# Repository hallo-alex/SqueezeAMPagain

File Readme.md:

# SqueezeAMPagain

As github annoys me with their 2FA policy I'm moving this to [codeberg](https://codeberg.org/hallo-alex/SqueezeAMPagain)

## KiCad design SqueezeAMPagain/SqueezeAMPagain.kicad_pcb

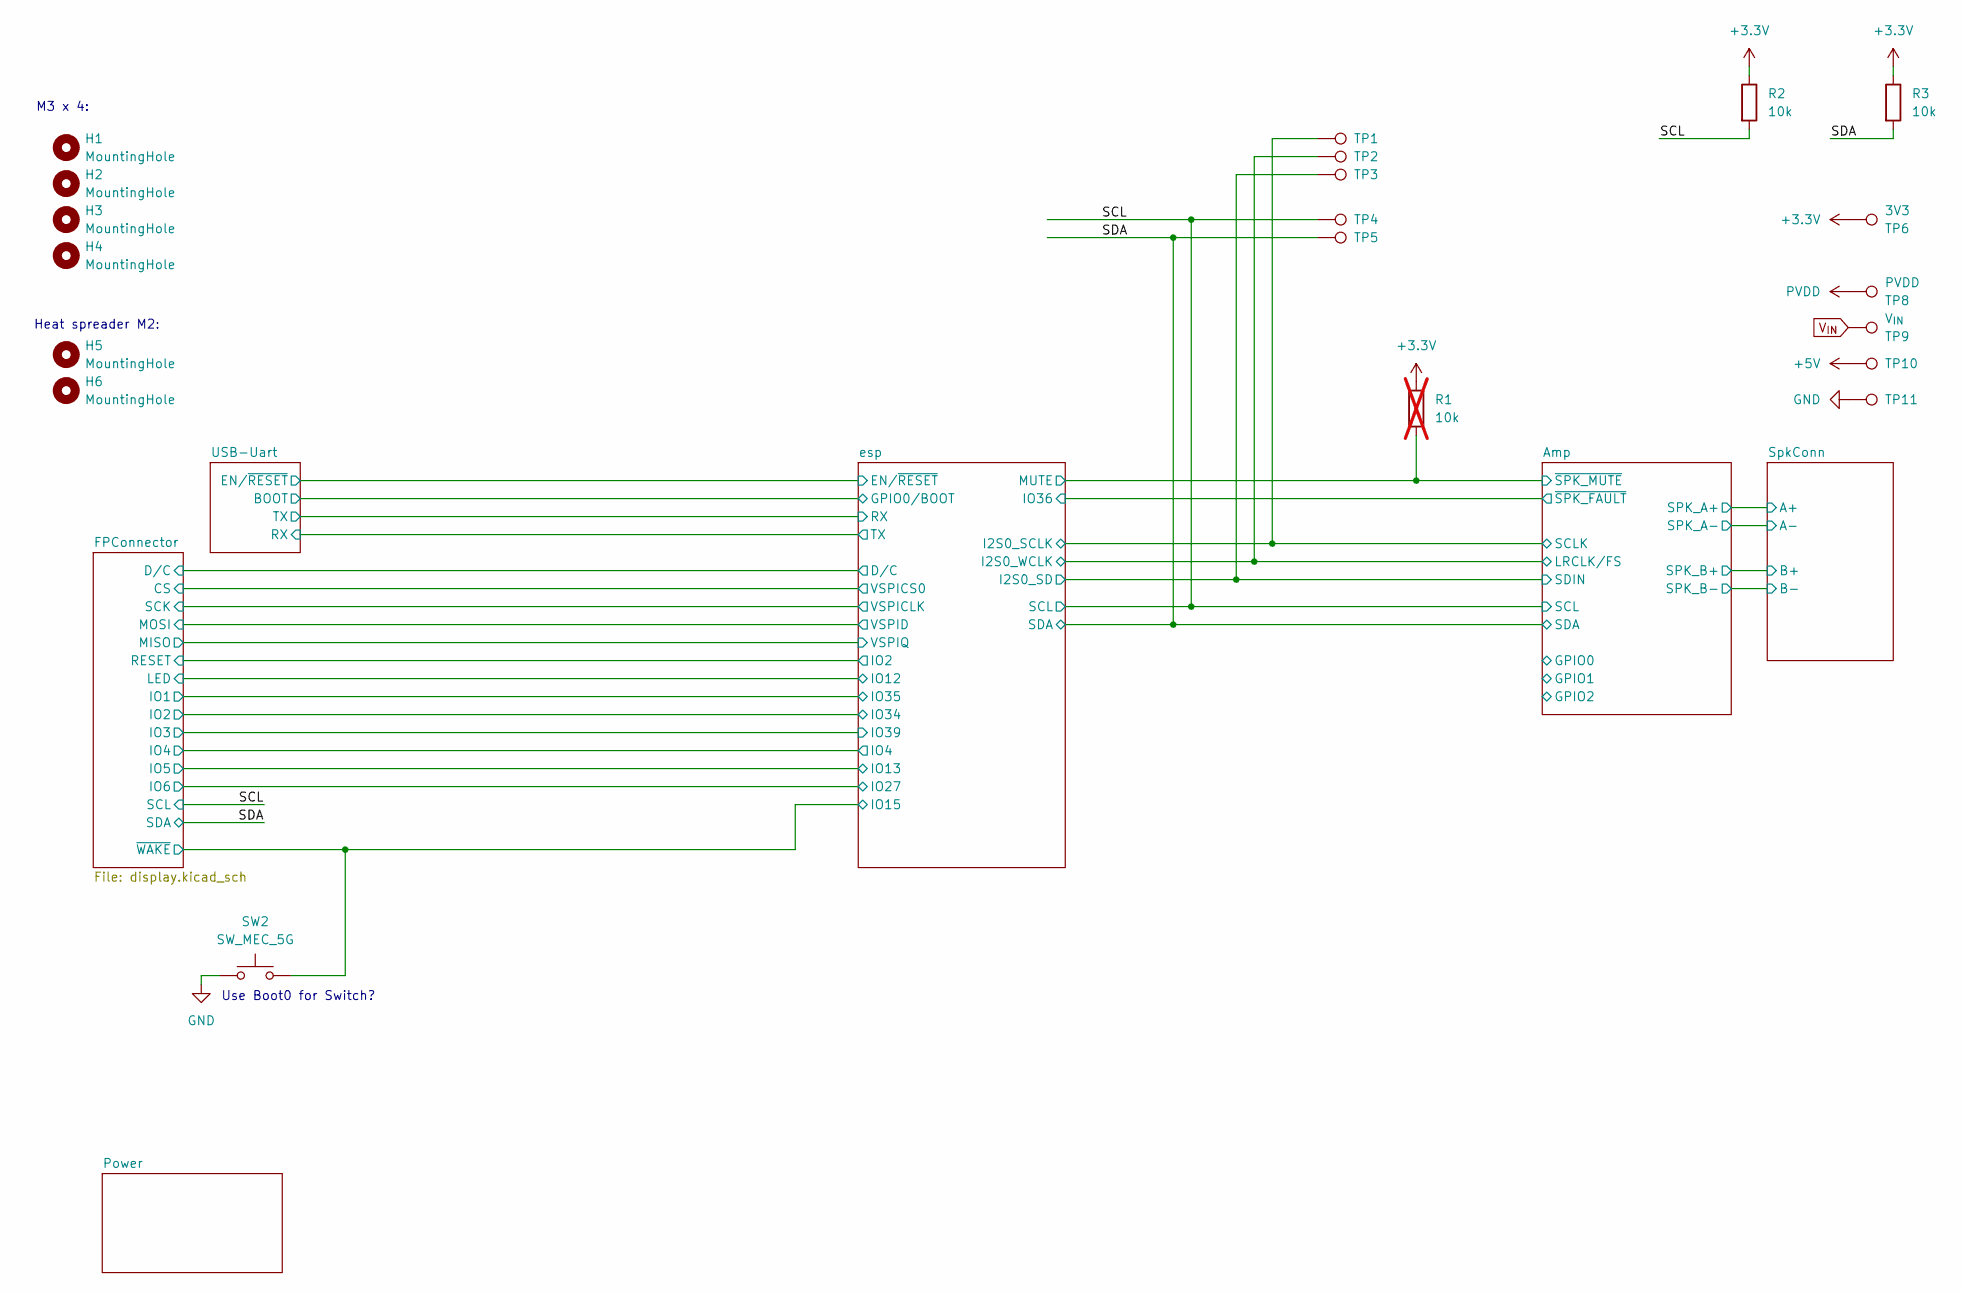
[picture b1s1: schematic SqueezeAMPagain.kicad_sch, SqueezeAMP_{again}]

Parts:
H1, H2, H3, H4: MountingHole; MountingHole_3.2mm_M3
H5, H6: MountingHole; MountingHole_2.5mm
R1: 10k; R_0402_1005Metric; JLCPCB# C25804; not fitted
R2, R3: 10k; R_0402_1005Metric; JLCPCB# C25804
SW2: SW_MEC_5G; SW_Push_1P1T_XKB_TS-1187A
TP1, TP2, TP3, TP4, TP5, TP10: TestPoint_Pad_D1.0mm
TP6: 3V3; TestPoint_Pad_D1.0mm
TP8: PVDD; TestPoint_Pad_D1.0mm
TP9: V_{IN}; TestPoint_Pad_D1.0mm
TP11: TestPoint_THTPad_D1.0mm_Drill0.5mm

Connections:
+3.3V: R1.1, R2.1, R3.1, TP6.1; also elsewhere on the board
+5V: TP10.1; also elsewhere on the board
/Amp/LRCLK/FS: TP2.1; also elsewhere on the board
/Amp/SCLK: TP1.1; also elsewhere on the board
/Amp/SDIN: TP3.1; also elsewhere on the board
/FPConnector/~WAKE: SW2.3 (B), SW2.4 (B); also elsewhere on the board
/SCL: R2.2, TP4.1; also elsewhere on the board
/SDA: R3.2, TP5.1; also elsewhere on the board
/esp/TMS: R1.2; also elsewhere on the board
GND: SW2.1 (A), SW2.2 (A), TP11.1; also elsewhere on the board
PVDD: TP8.1; also elsewhere on the board
V_{IN}: TP9.1

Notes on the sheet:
M3 x 4:
Use Boot0 for Switch?
Heat spreader M2:

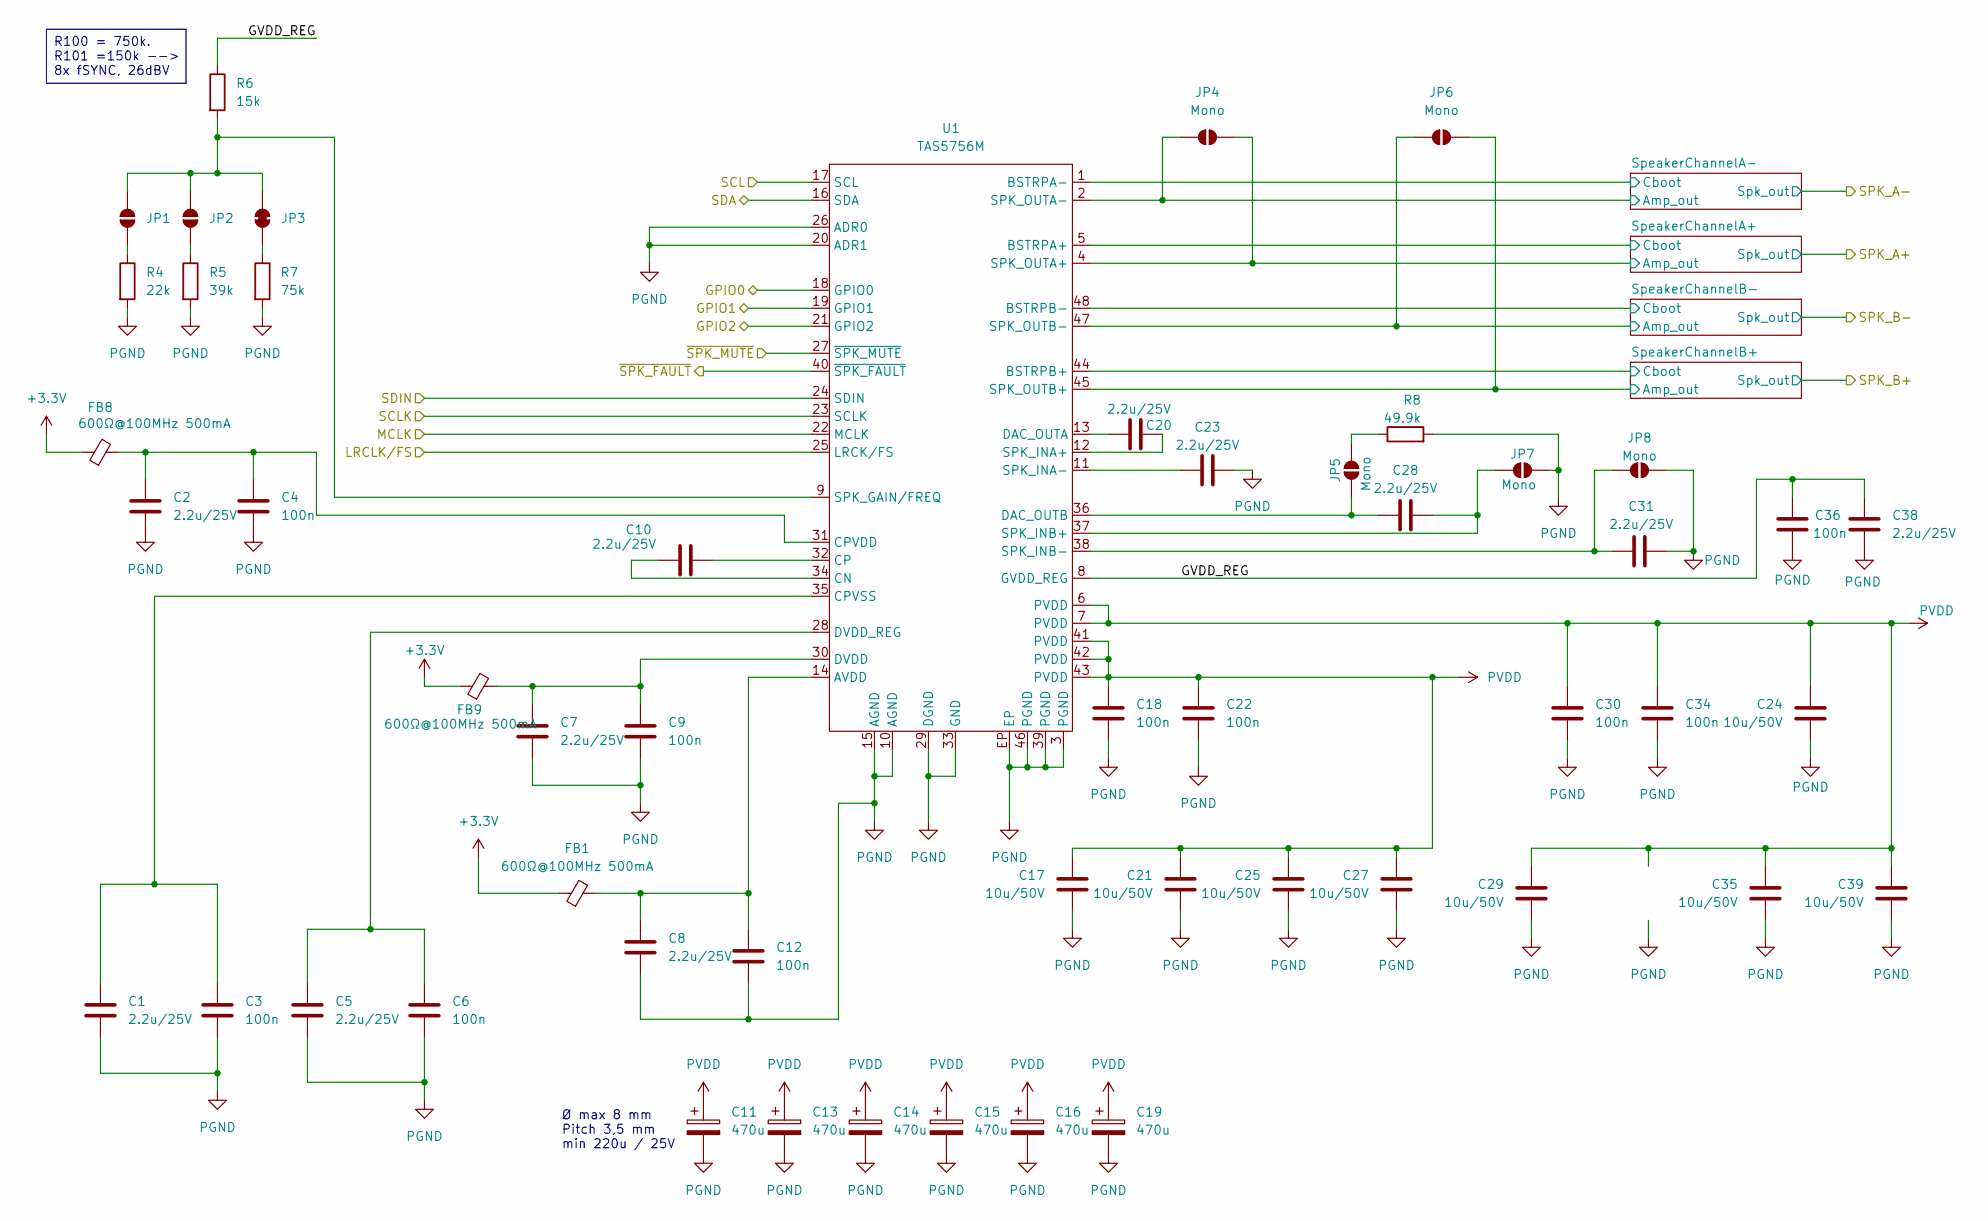
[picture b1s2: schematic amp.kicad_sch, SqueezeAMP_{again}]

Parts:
C1, C2, C5, C7, C8, C10, C20, C23, C28, C31, C38: 2.2u/25V; C_0805_2012Metric
C3, C4, C6, C9, C12: 100n; C_0402_1005Metric
C11, C13, C14, C15, C16, C19: 470u; CP_Radial_D8.0mm_P3.50mm
C17, C21, C24, C25, C27, C29, C35, C39: 10u/50V; C_1206_3216Metric
C18, C22, C30, C34, C36: 100n; C_0603_1608Metric
FB1, FB8, FB9: 600Ω@100MHz 500mA; L_0805_2012Metric; JLCPCB# C1017
JP1, JP2: SolderJumper_2_Open; SolderJumper-2_P1.3mm_Open_RoundedPad1.0x1.5mm
JP3: SolderJumper_2_Bridged; SolderJumper-2_P1.3mm_Bridged_RoundedPad1.0x1.5mm
JP4, JP5, JP6, JP7, JP8: Mono; SolderJumper-2_P1.3mm_Open_RoundedPad1.0x1.5mm
R4: 22k; R_0402_1005Metric; JLCPCB C31850
R5: 39k; R_0603_1608Metric; JLCPCB C23153
R6: 15k; R_0402_1005Metric; JLCPCB# C22809
R7: 75k; R_0603_1608Metric; JLCPCB C23242
R8: 49.9k; R_0402_1005Metric; JLCPCB# C23184
U1: TAS5756M; TSSOP-48_6.1x12.5mm_P0.5mm_EP

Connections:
+3.3V: FB1.1, FB8.1, FB9.1; also elsewhere on the board
/Amp/GPIO0: U1.18 (GPIO0)
/Amp/GPIO1: U1.19 (GPIO1)
/Amp/GPIO2: U1.21 (GPIO2)
/Amp/GVDD_REG: C36.1, C38.2, R6.1, U1.8 (GVDD_REG)
/Amp/LRCLK/FS: U1.25 (LRCK/FS); also elsewhere on the board
/Amp/MCLK: U1.22 (MCLK)
/Amp/SCLK: U1.23 (SCLK); also elsewhere on the board
/Amp/SDIN: U1.24 (SDIN); also elsewhere on the board
/Amp/SpeakerChannelA+/Amp_out: JP4.2 (B), U1.4 (SPK_OUTA+); also elsewhere on the board
/Amp/SpeakerChannelA+/Cboot: U1.5 (BSTRPA+); also elsewhere on the board
/Amp/SpeakerChannelA-/Amp_out: JP4.1 (A), U1.2 (SPK_OUTA-); also elsewhere on the board
/Amp/SpeakerChannelA-/Cboot: U1.1 (BSTRPA-); also elsewhere on the board
/Amp/SpeakerChannelB+/Amp_out: JP6.2 (B), U1.45 (SPK_OUTB+); also elsewhere on the board
/Amp/SpeakerChannelB+/Cboot: U1.44 (BSTRPB+); also elsewhere on the board
/Amp/SpeakerChannelB-/Amp_out: JP6.1 (A), U1.47 (SPK_OUTB-); also elsewhere on the board
/Amp/SpeakerChannelB-/Cboot: U1.48 (BSTRPB-); also elsewhere on the board
/Amp/~SPK_FAULT: U1.40 (~SPK_FAULT); also elsewhere on the board
/SCL: U1.17 (SCL); also elsewhere on the board
/SDA: U1.16 (SDA); also elsewhere on the board
/esp/TMS: U1.27 (~SPK_MUTE); also elsewhere on the board
unnamed: JP1.1 (A), R4.1
unnamed: JP1.2 (B), JP2.2 (B), JP3.2 (B), R6.2, U1.9 (SPK_GAIN/FREQ)
unnamed: JP2.1 (A), R5.1
unnamed: JP3.1 (A), R7.1
unnamed: C28.1, JP5.1 (A), U1.36 (DAC_OUTB)
unnamed: JP5.2 (B), R8.1
unnamed: C28.2, JP7.1 (A), U1.37 (SPK_INB+)
unnamed: C31.1, JP8.1 (A), U1.38 (SPK_INB-)
unnamed: C8.1, C12.1, FB1.2, U1.14 (AVDD)
unnamed: C10.2, U1.34 (CN)
unnamed: C10.1, U1.32 (CP)
unnamed: C2.1, C4.1, FB8.2, U1.31 (CPVDD)
unnamed: C1.1, C3.1, U1.35 (CPVSS)
unnamed: C20.1, U1.13 (DAC_OUTA)
unnamed: C7.1, C9.1, FB9.2, U1.30 (DVDD)
unnamed: C5.1, C6.1, U1.28 (DVDD_REG)
unnamed: C20.2, U1.12 (SPK_INA+)
unnamed: C23.1, U1.11 (SPK_INA-)
PGND: C1.2, C2.2, C3.2, C4.2, C5.2, C6.2, C7.2, C8.2, C9.2, C11.2, C12.2, C13.2, C14.2, C15.2, C16.2, C17.2, C18.2, C19.2, C21.2, C22.2, C23.2, C24.2, C25.2, C27.2, C29.2, C30.2, C31.2, C34.2, C35.2, C36.2, C38.1, C39.2, JP7.2 (B), JP8.2 (B), R4.2, R5.2, R7.2, R8.2, U1.3 (PGND), U1.10 (AGND), U1.15 (AGND), U1.20 (ADR1), U1.26 (ADR0), U1.29 (DGND), U1.33 (GND), U1.39 (PGND), U1.46 (PGND), U1.EP; also elsewhere on the board
PVDD: C11.1, C13.1, C14.1, C15.1, C16.1, C17.1, C18.1, C19.1, C21.1, C22.1, C24.1, C25.1, C27.1, C29.1, C30.1, C34.1, C35.1, C39.1, U1.6 (PVDD), U1.7 (PVDD), U1.41 (PVDD), U1.42 (PVDD), U1.43 (PVDD); also elsewhere on the board

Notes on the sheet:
Ø max 8 mm Pitch 3,5 mm min 220u / 25V
R100 = 750k. R101 =150k --> 8x fSYNC, 26dBV

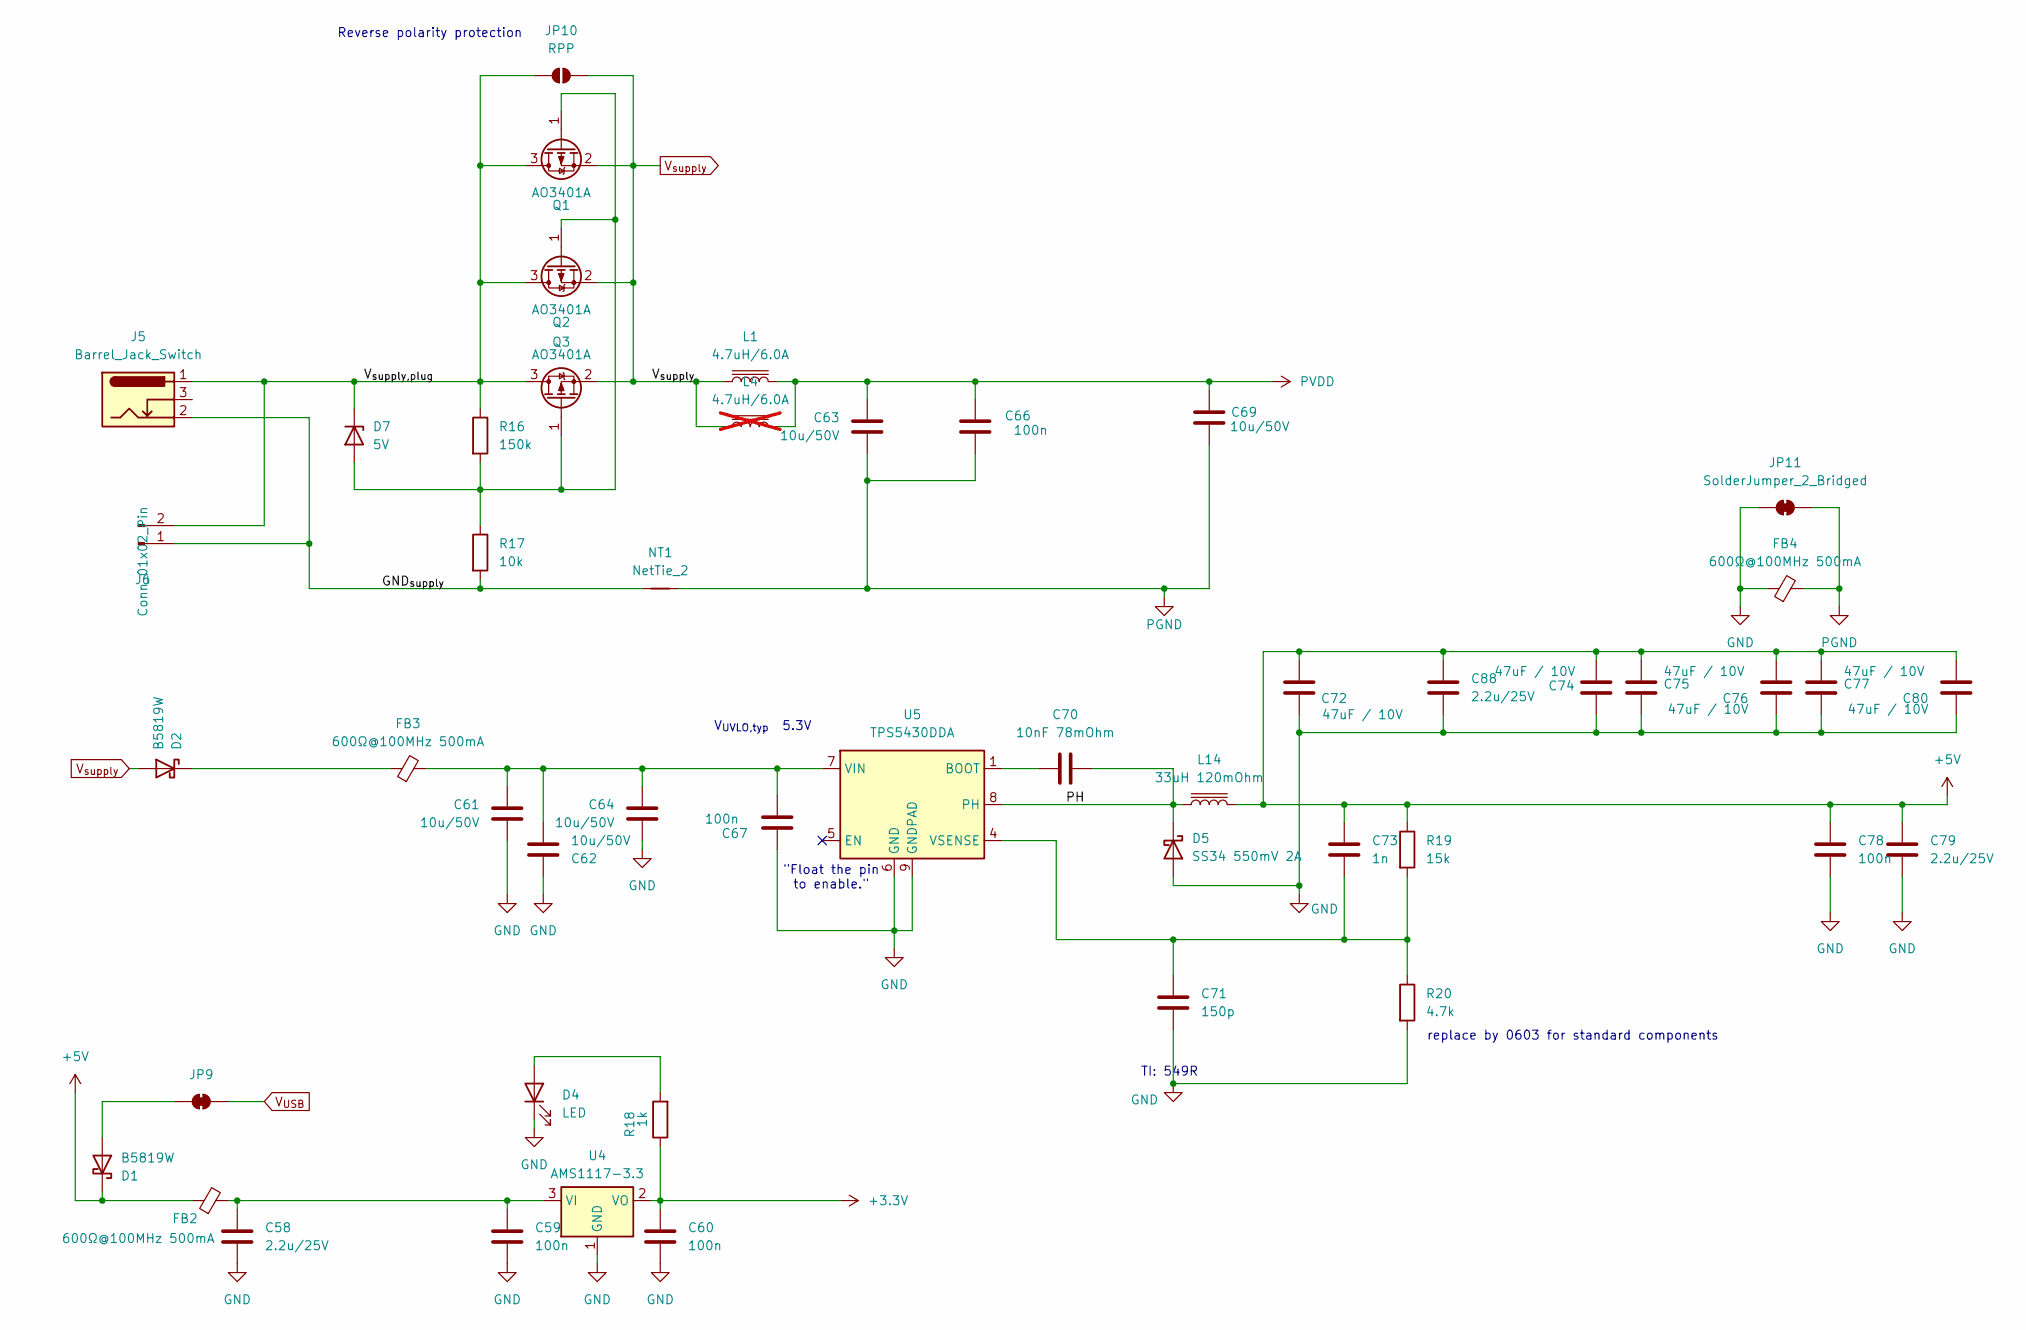
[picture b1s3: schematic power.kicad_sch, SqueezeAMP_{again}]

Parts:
C58, C79, C88: 2.2u/25V; C_0805_2012Metric
C59, C60, C78: 100n; C_0402_1005Metric
C61, C62, C63, C64, C69: 10u/50V; C_1206_3216Metric
C66, C67: 100n; C_0603_1608Metric
C70: 10nF 78mOhm; C_0603_1608Metric
C71: 150p; C_0603_1608Metric
C72, C74, C75, C76, C77, C80: 47uF / 10V; C_1206_3216Metric; JLCPCB# C96123
C73: 1n; C_0402_1005Metric
D1, D2: B5819W; D_SOD-123; JLCPCB# C8598
D4: LED; LED_0603_1608Metric
D5: SS34 550mV 2A; D_SMA; JLCPCB# C8678
D7: 5V; D_SOD-123
FB2, FB3, FB4: 600Ω@100MHz 500mA; L_0805_2012Metric; JLCPCB# C1017
J5: Barrel_Jack_Switch; BarrelJack_GCT_DCJ200-10-A_Horizontal
J6: Conn_01x02_Pin; PhoenixContact_MC_1,5_2-G-3.5_1x02_P3.50mm_Horizontal
JP9: SolderJumper_2_Bridged; SolderJumper-2_P1.3mm_Bridged_RoundedPad1.0x1.5mm
JP10: RPP; SolderJumper-2_P1.3mm_Open_RoundedPad1.0x1.5mm
JP11: SolderJumper_2_Bridged; SolderJumper-2_P1.3mm_Bridged2Bar_RoundedPad1.0x1.5mm
L1: 4.7uH/6.0A; L_Chilisin_BMRA00040420; mfr# 7447471047
L4: 4.7uH/6.0A; L_Radial_D8.7mm_P5.00mm_Fastron_07HCP; mfr# 7447471047; not fitted
L14: 33uH 120mOhm; L_Changjiang_FNR5020S; jlcpcb C5127240
NT1: NetTie_2; NetTie-2_SMD_Pad2.0mm
Q1, Q2, Q3: AO3401A; SOT-23; JLCPCB# C15127
R16: 150k; R_0603_1608Metric
R17: 10k; R_0402_1005Metric
R18: 1k; R_0402_1005Metric; JLCPCB# C23138
R19: 15k; R_0402_1005Metric; JLCPCB# C22809
R20: 4.7k; R_0402_1005Metric; JLCPCB# C23162
U4: AMS1117-3.3; SOT-223-3_TabPin2
U5: TPS5430DDA; TI_SO-PowerPAD-8_ThermalVias; JLCPCB# C9864

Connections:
+3.3V: C60.1, R18.1, U4.2 (VO); also elsewhere on the board
+5V: C72.1, C73.1, C74.2, C75.2, C76.1, C77.2, C78.1, C79.1, C80.1, C88.1, D1.1 (K), FB2.1, L14.2, R19.1; also elsewhere on the board
/Power/GND_{supply}: J5.2, J6.1, NT1.1, R17.2
/Power/PH: C70.2, D5.1 (K), L14.1, U5.8 (PH)
/Power/V_{supply,plug}: D7.1 (K), J5.1, J6.2, JP10.1 (A), Q1.3 (D), Q2.3 (D), Q3.3 (D), R16.1
GND: C58.2, C59.2, C60.2, C61.2, C62.1, C64.2, C67.1, C71.2, C72.2, C74.1, C75.1, C76.2, C77.1, C78.2, C79.2, C80.2, C88.2, D4.1 (K), D5.2 (A), FB4.1, JP11.1 (A), R20.2, U4.1 (GND), U5.6 (GND), U5.9 (GNDPAD); also elsewhere on the board
unnamed: D1.2 (A), JP9.2 (B)
unnamed: D2.1 (K), FB3.1
unnamed: D4.2 (A), R18.2
unnamed: D7.2 (A), Q1.1 (G), Q2.1 (G), Q3.1 (G), R16.2, R17.1
unnamed: C58.1, C59.1, FB2.2, U4.3 (VI)
unnamed: C70.1, U5.1 (BOOT)
unnamed: C61.1, C62.2, C64.1, C67.2, FB3.2, U5.7 (VIN)
unnamed: C71.1, C73.2, R19.2, R20.1, U5.4 (VSENSE)
PGND: C63.2, C66.2, C69.2, FB4.2, JP11.2 (B), NT1.2; also elsewhere on the board
PVDD: C63.1, C66.1, C69.1, L1.2, L4.2; also elsewhere on the board
V_{USB}: JP9.1 (A); also elsewhere on the board
V_{supply}: D2.2 (A), JP10.2 (B), L1.1, L4.1, Q1.2 (S), Q2.2 (S), Q3.2 (S)

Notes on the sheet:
Reverse polarity protection
"Float the pin to enable."
replace by 0603 for standard components
TI: 549R
V_{UVLO,typ} 5.3V

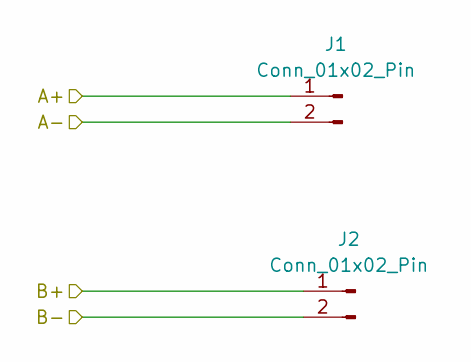
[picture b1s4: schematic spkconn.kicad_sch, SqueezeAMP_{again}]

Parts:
J1, J2: Conn_01x02_Pin; PhoenixContact_MC_1,5_2-G-3.5_1x02_P3.50mm_Horizontal

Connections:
/Amp/SPK_A+: J1.1; also elsewhere on the board
/Amp/SPK_A-: J1.2; also elsewhere on the board
/Amp/SPK_B+: J2.1; also elsewhere on the board
/Amp/SPK_B-: J2.2; also elsewhere on the board

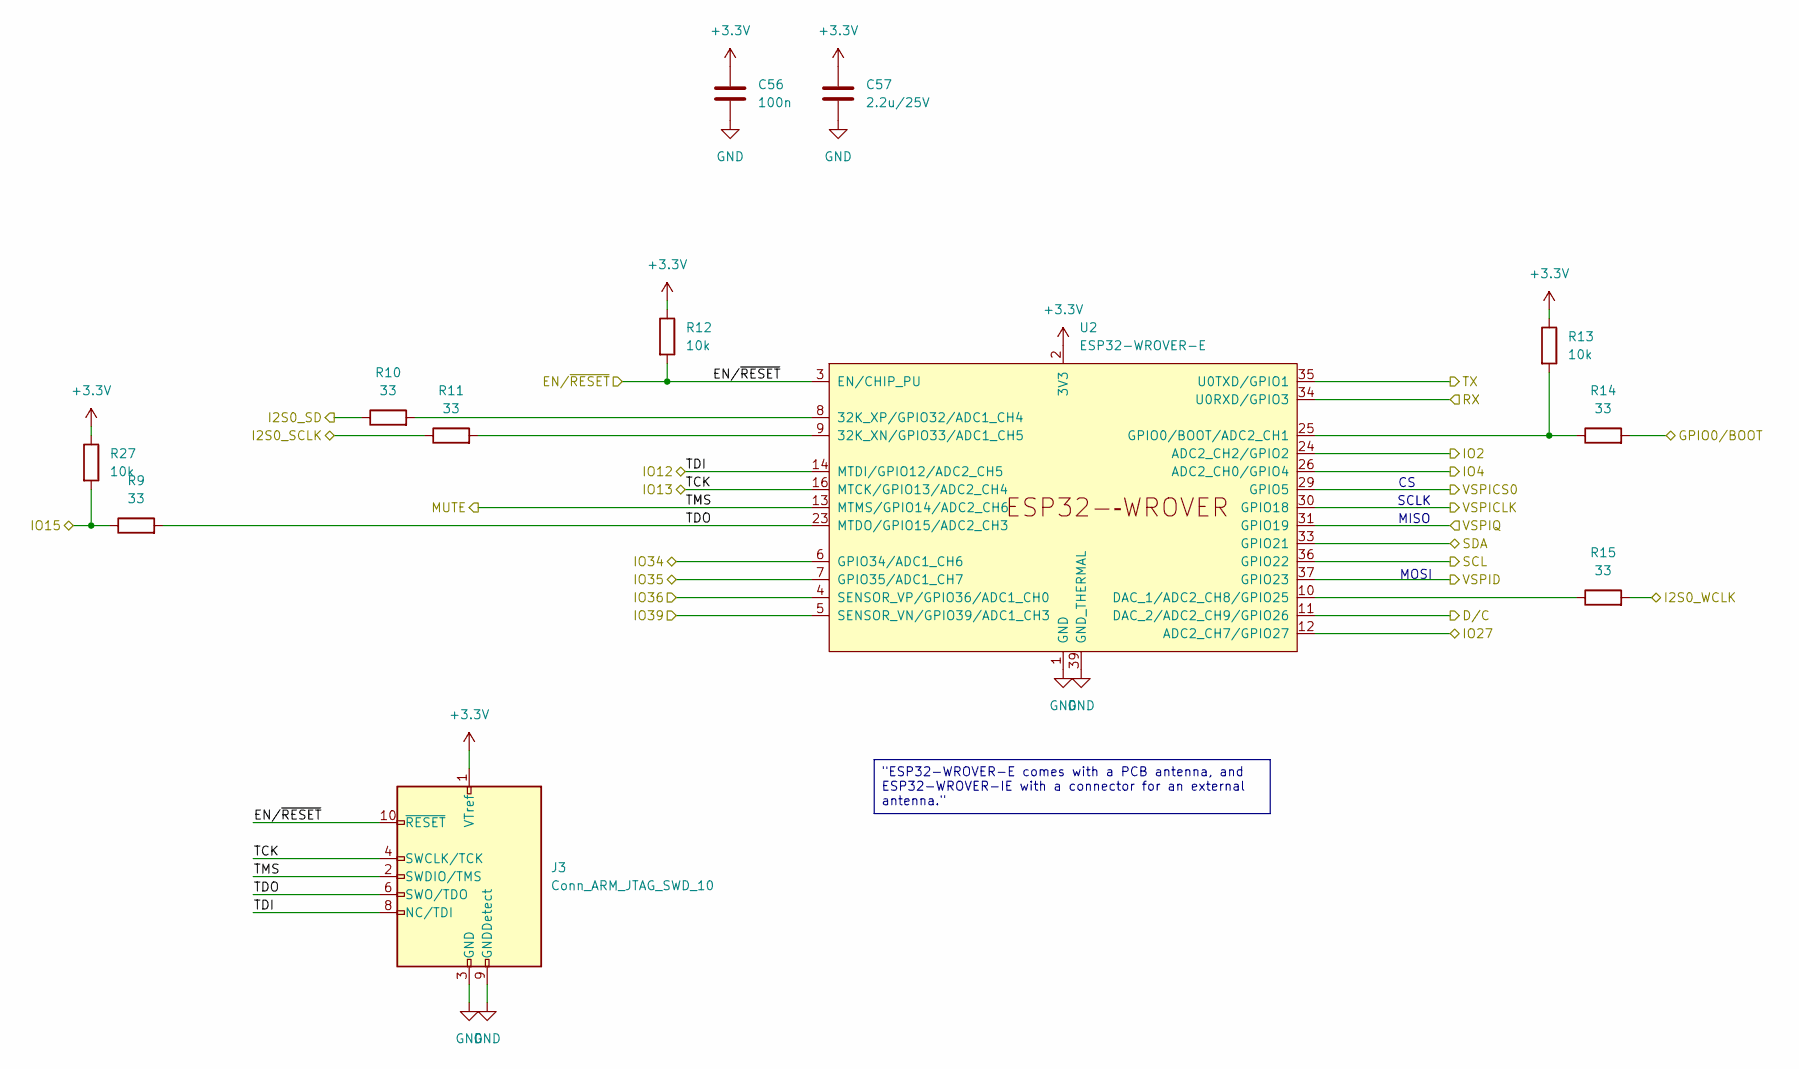
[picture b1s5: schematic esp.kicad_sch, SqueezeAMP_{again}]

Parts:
C56: 100n; C_0402_1005Metric
C57: 2.2u/25V; C_0805_2012Metric
J3: Conn_ARM_JTAG_SWD_10; PinHeader_2x05_P1.27mm_Vertical_SMD
R9, R10, R11, R14, R15: 33; R_0402_1005Metric; JLCPCB C25105
R12, R13, R27: 10k; R_0402_1005Metric
U2: ESP32-WROVER-E; ESP32-WROVER-E_ThermalVias

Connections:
+3.3V: C56.1, C57.1, J3.1 (VTref), R12.1, R13.1, R27.1, U2.2 (3V3); also elsewhere on the board
/Amp/LRCLK/FS: R15.2; also elsewhere on the board
/Amp/SCLK: R11.1; also elsewhere on the board
/Amp/SDIN: R10.1; also elsewhere on the board
/Amp/~SPK_FAULT: U2.4 (SENSOR_VP/GPIO36/ADC1_CH0); also elsewhere on the board
/FPConnector/CS: U2.29 (GPIO5); also elsewhere on the board
/FPConnector/D/C: U2.11 (DAC_2/ADC2_CH9/GPIO26); also elsewhere on the board
/FPConnector/IO1: U2.7 (GPIO35/ADC1_CH7); also elsewhere on the board
/FPConnector/IO2: U2.6 (GPIO34/ADC1_CH6); also elsewhere on the board
/FPConnector/IO3: U2.5 (SENSOR_VN/GPIO39/ADC1_CH3); also elsewhere on the board
/FPConnector/IO4: U2.26 (ADC2_CH0/GPIO4); also elsewhere on the board
/FPConnector/IO6: U2.12 (ADC2_CH7/GPIO27); also elsewhere on the board
/FPConnector/MISO: U2.31 (GPIO19); also elsewhere on the board
/FPConnector/MOSI: U2.37 (GPIO23); also elsewhere on the board
/FPConnector/RESET: U2.24 (ADC2_CH2/GPIO2); also elsewhere on the board
/FPConnector/SCK: U2.30 (GPIO18); also elsewhere on the board
/FPConnector/~WAKE: R9.1, R27.2; also elsewhere on the board
/SCL: U2.36 (GPIO22); also elsewhere on the board
/SDA: U2.33 (GPIO21); also elsewhere on the board
/USB-Uart/BOOT: R14.2; also elsewhere on the board
/USB-Uart/EN/~RESET: J3.10 (~RESET), R12.2, U2.3 (EN/CHIP_PU); also elsewhere on the board
/USB-Uart/RX: U2.35 (U0TXD/GPIO1); also elsewhere on the board
/USB-Uart/TX: U2.34 (U0RXD/GPIO3); also elsewhere on the board
/esp/TCK: J3.4 (SWCLK/TCK), U2.16 (MTCK/GPIO13/ADC2_CH4); also elsewhere on the board
/esp/TDI: J3.8 (NC/TDI), U2.14 (MTDI/GPIO12/ADC2_CH5); also elsewhere on the board
/esp/TDO: J3.6 (SWO/TDO), R9.2, U2.23 (MTDO/GPIO15/ADC2_CH3)
/esp/TMS: J3.2 (SWDIO/TMS), U2.13 (MTMS/GPIO14/ADC2_CH6); also elsewhere on the board
GND: C56.2, C57.2, J3.3 (GND), J3.5 (GND), J3.9 (GNDDetect), U2.1 (GND), U2.15 (GND), U2.38 (GND), U2.39 (GND_THERMAL); also elsewhere on the board
unnamed: R11.2, U2.9 (32K_XN/GPIO33/ADC1_CH5)
unnamed: R10.2, U2.8 (32K_XP/GPIO32/ADC1_CH4)
unnamed: R15.1, U2.10 (DAC_1/ADC2_CH8/GPIO25)
unnamed: R13.2, R14.1, U2.25 (GPIO0/BOOT/ADC2_CH1)

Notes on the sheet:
MOSI
SCLK
MISO
"ESP32-WROVER-E comes with a PCB antenna, and ESP32-WROVER-IE with a connector for an external antenna."

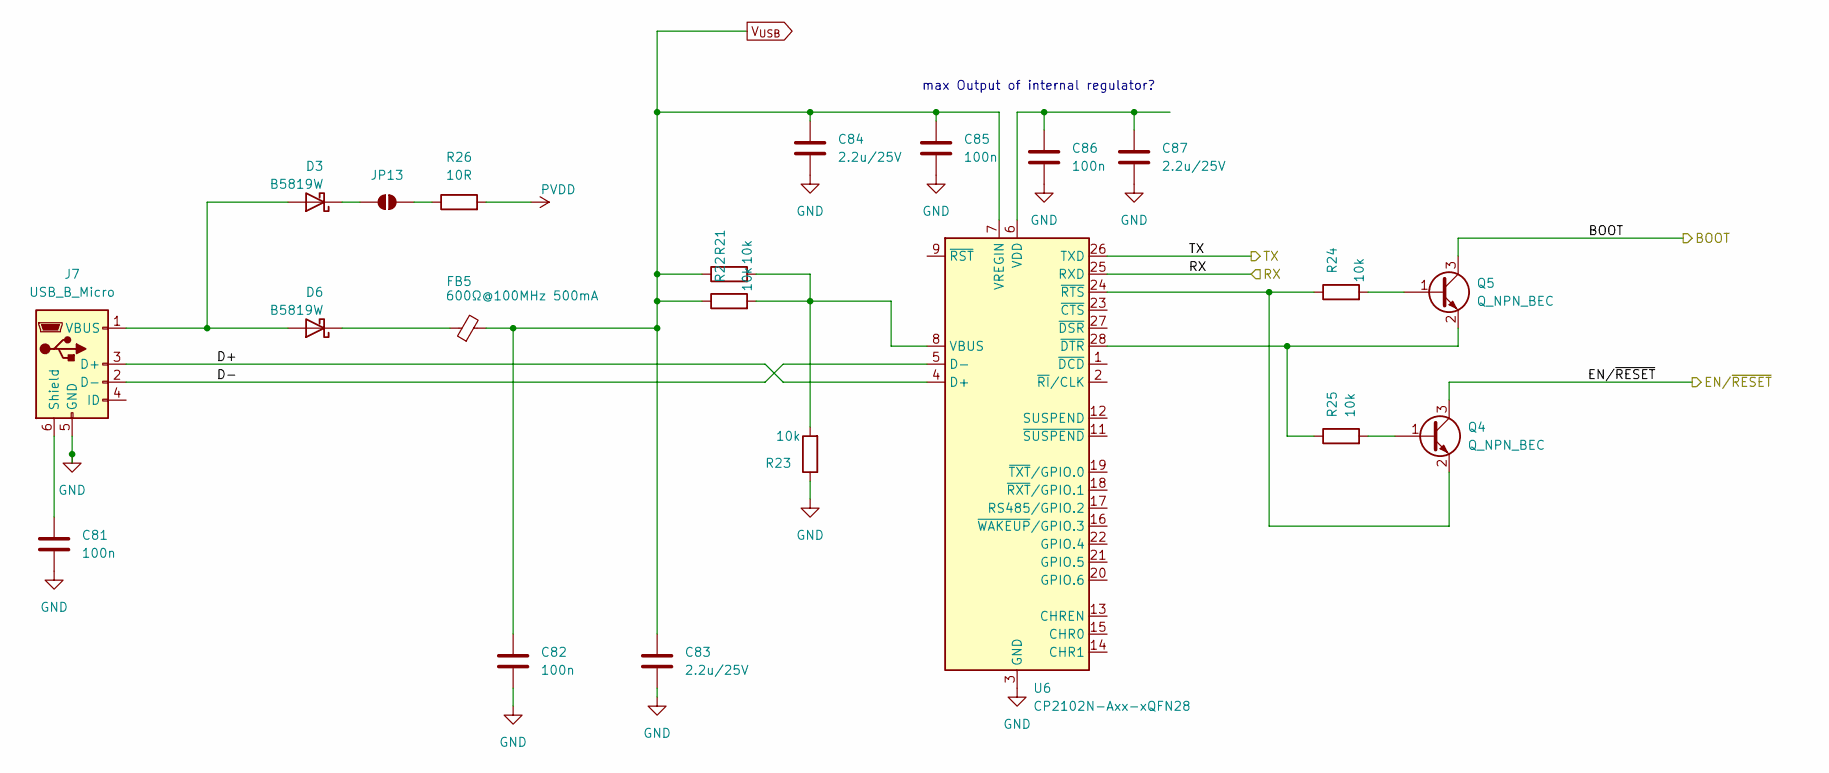
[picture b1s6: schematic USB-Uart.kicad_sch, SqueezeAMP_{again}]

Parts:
C81, C82, C85, C86: 100n; C_0402_1005Metric
C83, C84, C87: 2.2u/25V; C_0805_2012Metric
D3, D6: B5819W; D_SOD-123; JLCPCB# C8598
FB5: 600Ω@100MHz 500mA; L_0805_2012Metric; JLCPCB# C1017
J7: USB_B_Micro; usb_micro_xnj_073
JP13: SolderJumper_2_Open; SolderJumper-2_P1.3mm_Open_RoundedPad1.0x1.5mm
Q4, Q5: Q_NPN_BEC; SOT-23
R21, R22, R23: 10k; R_0402_1005Metric; JLCPCB# C25804
R24, R25: 10k; R_0402_1005Metric
R26: 10R; R_1206_3216Metric_Pad1.30x1.75mm_HandSolder
U6: CP2102N-Axx-xQFN28; QFN-28-1EP_5x5mm_P0.5mm_EP3.35x3.35mm

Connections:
/USB-Uart/BOOT: Q5.3 (C); also elsewhere on the board
/USB-Uart/D+: J7.3 (D+), U6.4 (D+)
/USB-Uart/D-: J7.2 (D-), U6.5 (D-)
/USB-Uart/EN/~RESET: Q4.3 (C); also elsewhere on the board
/USB-Uart/RX: U6.25 (RXD); also elsewhere on the board
/USB-Uart/TX: U6.26 (TXD); also elsewhere on the board
GND: C81.2, C82.2, C83.2, C84.2, C85.2, C86.2, C87.2, J7.5 (GND), R23.1, U6.3 (GND), U6.29 (GND); also elsewhere on the board
unnamed: D3.2 (A), D6.2 (A), J7.1 (VBUS)
unnamed: D3.1 (K), JP13.2 (B)
unnamed: D6.1 (K), FB5.1
unnamed: C81.1, J7.6 (Shield)
unnamed: JP13.1 (A), R26.1
unnamed: Q4.1 (B), R25.2
unnamed: Q4.2 (E), R24.1, U6.24 (~RTS)
unnamed: Q5.1 (B), R24.2
unnamed: Q5.2 (E), R25.1, U6.28 (~DTR)
unnamed: R21.2, R22.2, R23.2, U6.8 (VBUS)
unnamed: C86.1, C87.1, U6.6 (VDD)
PVDD: R26.2; also elsewhere on the board
V_{USB}: C82.1, C83.1, C84.1, C85.1, FB5.2, R21.1, R22.1, U6.7 (VREGIN); also elsewhere on the board

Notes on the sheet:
max Output of internal regulator?

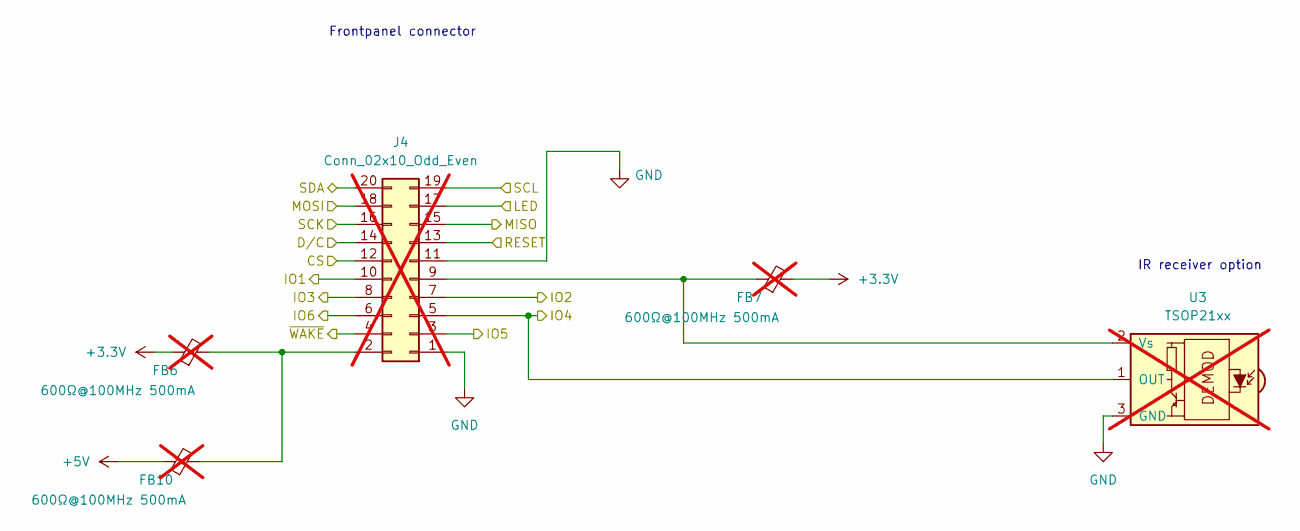
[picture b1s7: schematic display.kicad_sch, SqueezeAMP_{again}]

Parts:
FB6, FB7, FB10: 600Ω@100MHz 500mA; L_0805_2012Metric; JLCPCB# C1017; not fitted
J4: Conn_02x10_Odd_Even; IDC-Header_2x10_P2.54mm_Horizontal; not fitted
U3: TSOP21xx; Vishay_MOLD-3Pin; not fitted

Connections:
+3.3V: FB6.1, FB7.2; also elsewhere on the board
+5V: FB10.1; also elsewhere on the board
/FPConnector/CS: J4.12; also elsewhere on the board
/FPConnector/D/C: J4.14; also elsewhere on the board
/FPConnector/IO1: J4.10; also elsewhere on the board
/FPConnector/IO2: J4.7; also elsewhere on the board
/FPConnector/IO3: J4.8; also elsewhere on the board
/FPConnector/IO4: J4.5, U3.1 (OUT); also elsewhere on the board
/FPConnector/IO6: J4.6; also elsewhere on the board
/FPConnector/MISO: J4.15; also elsewhere on the board
/FPConnector/MOSI: J4.18; also elsewhere on the board
/FPConnector/RESET: J4.13; also elsewhere on the board
/FPConnector/SCK: J4.16; also elsewhere on the board
/FPConnector/~WAKE: J4.4; also elsewhere on the board
/SCL: J4.19; also elsewhere on the board
/SDA: J4.20; also elsewhere on the board
/esp/TCK: J4.3; also elsewhere on the board
/esp/TDI: J4.17; also elsewhere on the board
GND: J4.1, J4.11, U3.3 (GND); also elsewhere on the board
unnamed: FB6.2, FB10.2, J4.2
unnamed: FB7.1, J4.9, U3.2 (Vs)

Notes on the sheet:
IR receiver option
Frontpanel connector

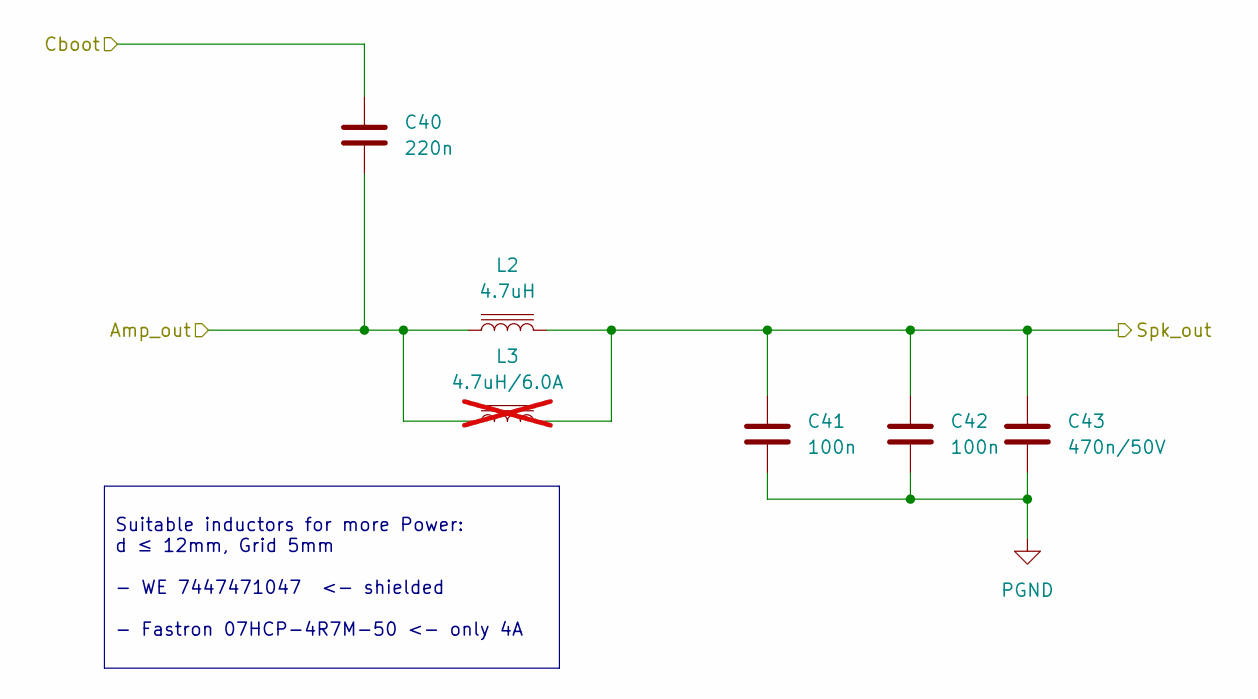
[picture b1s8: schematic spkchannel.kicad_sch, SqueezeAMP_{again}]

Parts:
C40: 220n; C_0603_1608Metric; JLCPCB# C5378
C41, C42: 100n; C_0603_1608Metric; JLCPCB# C14663
C43: 470n/50V; C_0805_2012Metric
L2: 4.7uH; L_Chilisin_BMRA00040420; mfr# 7447471047
L3: 4.7uH/6.0A; L_Radial_D8.7mm_P5.00mm_Fastron_07HCP; mfr# 7447471047; not fitted

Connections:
/Amp/SPK_A-: C41.1, C42.1, C43.1, L2.2, L3.2; also elsewhere on the board
/Amp/SpeakerChannelA-/Amp_out: C40.2, L2.1, L3.1; also elsewhere on the board
/Amp/SpeakerChannelA-/Cboot: C40.1; also elsewhere on the board
PGND: C41.2, C42.2, C43.2; also elsewhere on the board

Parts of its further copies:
C44, C48, C52: 220n; C_0603_1608Metric; JLCPCB# C5378
C45, C46, C49, C50, C53, C54: 100n; C_0603_1608Metric; JLCPCB# C14663
C47, C51, C55: 470n/50V; C_0805_2012Metric
L6, L9, L12: 4.7uH/6.0A; L_Radial_D8.7mm_P5.00mm_Fastron_07HCP; mfr# 7447471047; not fitted

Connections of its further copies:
/Amp/SPK_A+: C45.1, C46.1, C47.1, L6.2; also elsewhere on the board
/Amp/SPK_B+: C53.1, C54.1, C55.1, L12.2; also elsewhere on the board
/Amp/SPK_B-: C49.1, C50.1, C51.1, L9.2; also elsewhere on the board
/Amp/SpeakerChannelA+/Amp_out: C44.2, L6.1; also elsewhere on the board
/Amp/SpeakerChannelA+/Cboot: C44.1; also elsewhere on the board
/Amp/SpeakerChannelB+/Amp_out: C52.2, L12.1; also elsewhere on the board
/Amp/SpeakerChannelB+/Cboot: C52.1; also elsewhere on the board
/Amp/SpeakerChannelB-/Amp_out: C48.2, L9.1; also elsewhere on the board
/Amp/SpeakerChannelB-/Cboot: C48.1; also elsewhere on the board
PGND: C45.2, C46.2, C47.2, C49.2, C50.2, C51.2, C53.2, C54.2, C55.2; also elsewhere on the board

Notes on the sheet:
Suitable inductors for more Power: d ≤ 12mm, Grid 5mm - WE 7447471047 <- shielded - Fastron 07HCP-4R7M-50 <- only 4A

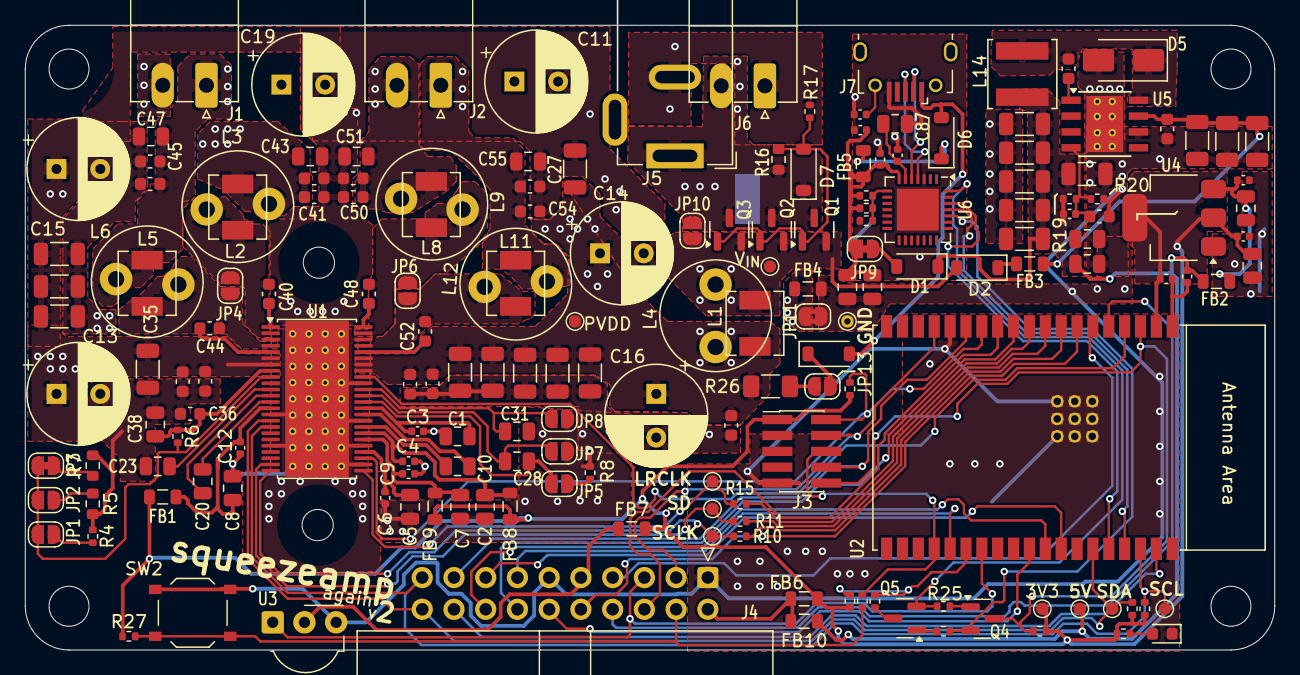
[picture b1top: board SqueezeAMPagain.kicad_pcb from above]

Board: 2 copper layers, 100.0 x 50.0 mm, 185 parts (1 on the bottom side), 94 nets.

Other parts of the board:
L5, L8, L11: 4.7uH/6.0A; L_Chilisin_BMRA00040420

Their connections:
/Amp/SPK_A+: L5.2; also elsewhere on the board
/Amp/SPK_B+: L11.2; also elsewhere on the board
/Amp/SPK_B-: L8.2; also elsewhere on the board
/Amp/SpeakerChannelA+/Amp_out: L5.1; also elsewhere on the board
/Amp/SpeakerChannelB+/Amp_out: L11.1; also elsewhere on the board
/Amp/SpeakerChannelB-/Amp_out: L8.1; also elsewhere on the board
